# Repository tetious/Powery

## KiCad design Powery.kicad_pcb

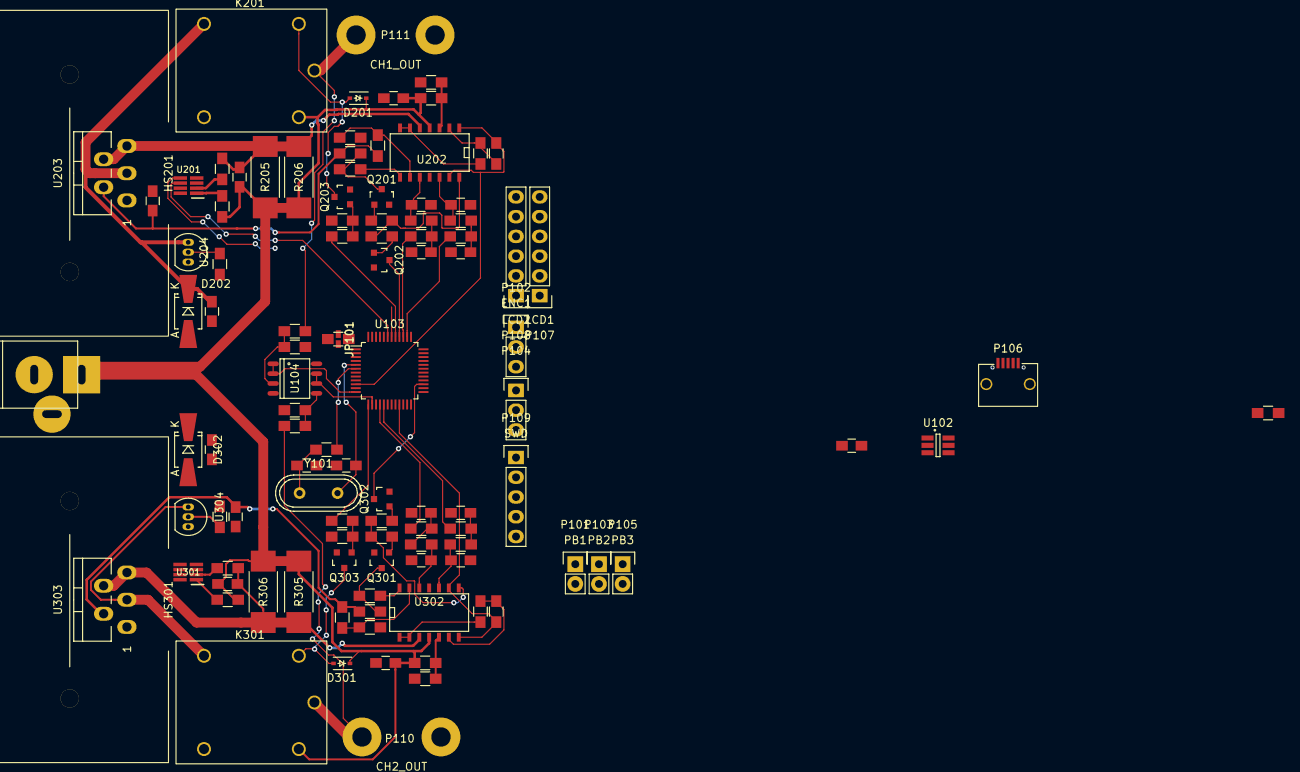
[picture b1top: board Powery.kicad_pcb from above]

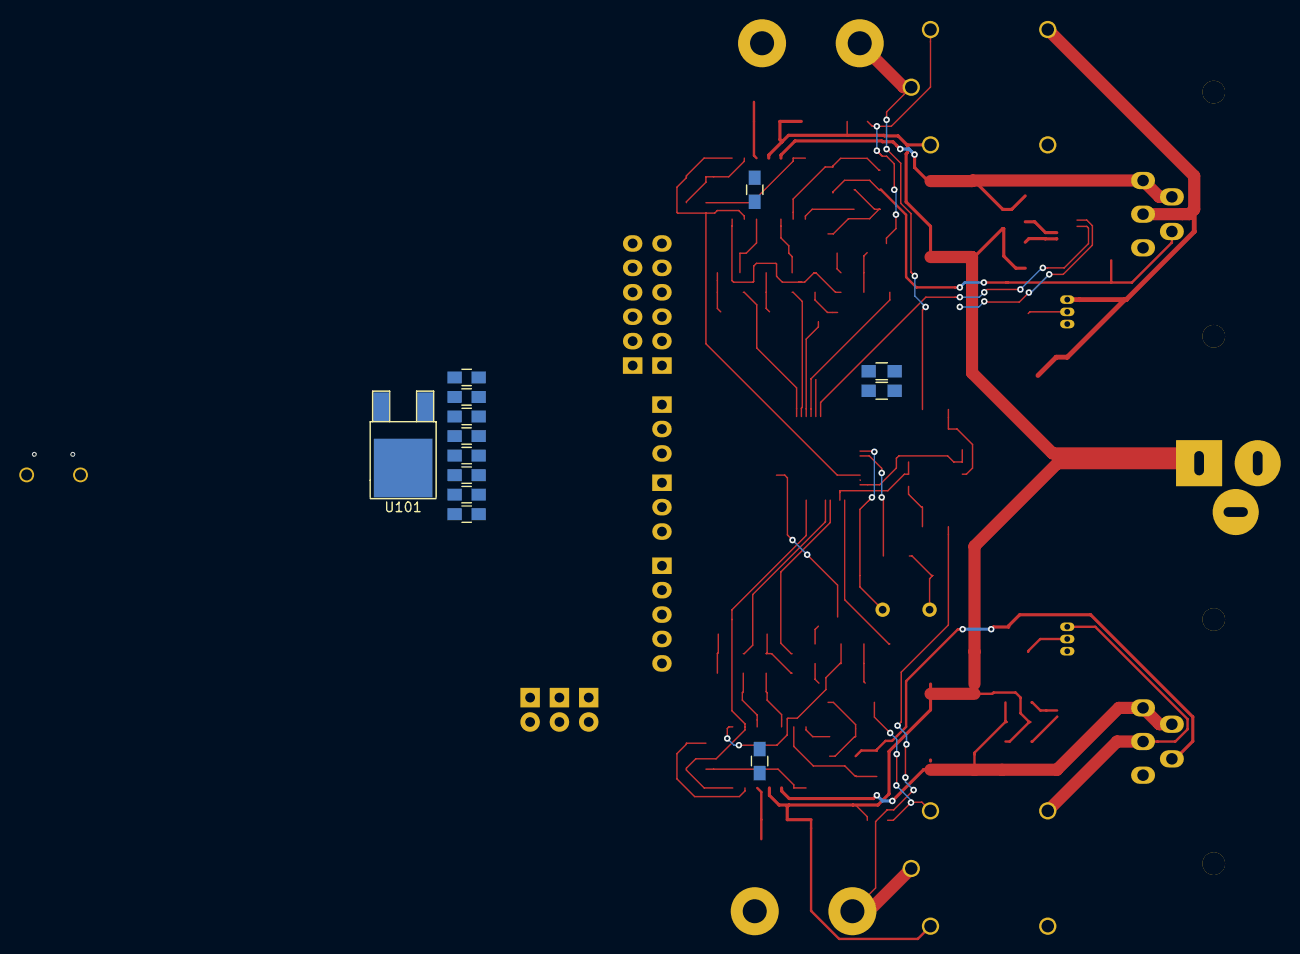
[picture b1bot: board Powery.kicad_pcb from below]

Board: 2 copper layers, 120 parts (13 on the bottom side), 87 nets.

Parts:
C101, C207, C208, C209, C307, C308, C309: 10uf; C_0805_HandSoldering
C102: 4.7uf; C_0805_HandSoldering
C103, C104, C105, C106, C107: 100nf; C_0805_HandSoldering
C108: 10nf; C_0805_HandSoldering
C109, C206, C306: 1uf; C_0805_HandSoldering
C110, C111: 20pf; C_0805_HandSoldering
C201, C301: NP; C_0805_HandSoldering
C202, C203, C204, C205, C302, C303, C304, C305: 0.1u; C_0805_HandSoldering
CON101: BARREL_JACK; JACK_ALIM
D201, D301: D; SOD-323
D202, D302: D; SMA-SMB_Universal_Handsoldering
HS201, HS301: HEATSINK; HS-TO220-20W
JP101: Jumper_NO_Small; MADW__SMD-solder-bridge-narrow
K201, K301: RELAY-SPDT; RELAY-SRD
P101: PB1; Pin_Header_Straight_1x02
P102: ENC1; Pin_Header_Straight_1x03
P103: PB2; Pin_Header_Straight_1x02
P104: ENC2; Pin_Header_Straight_1x03
P105: PB3; Pin_Header_Straight_1x02
P106: USB_OTG; USB_Micro-B-ebay
P107: LCD1; Pin_Header_Straight_1x06
P108: LCD2; Pin_Header_Straight_1x06
P109: SWD; Pin_Header_Straight_1x05
P110: CH2_OUT; WireConnection_2.50mmDrill
P111: CH1_OUT; WireConnection_2.50mmDrill
Q201, Q202, Q203, Q301, Q302, Q303: MMBT3904; SOT-23
R101, R102: 2.2k; R_0805_HandSoldering
R103: 4.7k; R_0805_HandSoldering
R104, R108, R109, R209, R212, R214, R215, R216, R220, R309, R312, R314, R315, R316, R320: 10k; R_0805_HandSoldering
R105: 220; R_0805_HandSoldering
R106, R107, R211, R311: 4.3k; R_0805_HandSoldering
R201, R202, R301, R302: 0; R_0805_HandSoldering
R203, R204, R207, R208, R210, R213, R303, R304, R307, R308, R310, R313: 100k; R_0805_HandSoldering
R205, R206, R305, R306: 0.22; R_2512_HandSoldering
R217, R219, R317, R319: 1k; R_0805_HandSoldering
R218, R221, R318, R321: 100; R_0805_HandSoldering
U101: LM1117; TO-252-2Lead
U102: AOZ8904; SOT-23-6_Handsoldering
U103: STM32F103C8Tx; LQFP-48_7x7mm_Pitch0.5mm
U104: LM258W; SO-8
U201, U301: INA219-SOT23; SOT-23-8
U202, U302: LM324; SOIC-14_N
U203, U303: LT3083; Pentawatt_Neutral_Staggered_Verical_TO220-5-T05D
U204, U304: LM334Z/NOPB; TO-92_Inline_Narrow_Oval
Y101: 8mhz; Crystal_HC49-U_Vertical

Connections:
+3V3: C102.1, C103.1, C104.1, C105.1, C106.1, C107.1, C108.1, C109.1, P107.1, P108.1, P109.1, R101.2, R102.1, R103.2, R104.1, U101.2, U103.1, U103.9, U103.24, U103.36, U103.48, U201.4, U301.4, U301.8
+12V: C101.1, C201.2, C206.1, C301.2, C306.1, CON101.1, D201.1, D301.1, K201.C1, K301.C1, R201.2, R205.2, R206.2, R209.2, R301.2, R305.2, R306.2, R309.2, U101.3, U104.8, U202.4, U302.4
/C1-I-LMT: Q202.3, U103.40
/C1-I-PWM: R204.2, U103.38
/C1-I-SENSE: R213.1, U103.10, U202.1, U202.13
/C1-V-PWM: R203.2, U103.39
/C1-V-SENSE: U103.12, U104.1, U104.2
/C2-I-LMT: Q302.3, U103.27
/C2-I-PWM: R304.2, U103.17
/C2-I-SENSE: R313.1, U103.21, U302.7, U302.9
/C2-V-PWM: R303.2, U103.16
/C2-V-SENSE: U103.14, U104.6, U104.7
/CH1_PWR: R219.2, U103.41
/CH2_PWR: R319.2, U103.13
/Channel1/12v-AS: C201.1, C207.2, R202.2, R205.1, R206.1, U202.5, U203.4, U203.5
/Channel1/OUT: K201.1, P111.1, R106.2
/Channel1/REG-OUT: C209.2, D202.1, K201.3, U203.3, U204.1
/Channel1/SET: C208.2, R214.1, R218.1, U203.2
/Channel2/12v-AS: C301.1, C307.2, R302.2, R305.1, R306.1, U302.3, U303.4, U303.5
/Channel2/OUT: K301.1, P110.1, R107.2
/Channel2/REG-OUT: C309.2, D302.1, K301.3, U303.3, U304.1
/Channel2/SET: C308.2, R314.1, R318.1, U303.2
/ENC_1A: P102.1, U103.45
/ENC_1B: P102.2, U103.46
/ENC_1PB: P102.3, U103.25
/ENC_2A: P104.1, U103.30
/ENC_2B: P104.2, U103.31
/ENC_2PB: P104.3, U103.29
/LCD1_CS: P107.3, U103.22
/LCD1_MD: P107.2, U103.15
/LCD2_CS: P108.3, U103.18
/LCD2_MD: P108.2, U103.19
/NRST: P109.5, U103.7
/PB_1: P101.1, U103.2
/PB_2: P103.1, U103.3
/PB_3: P105.1, U103.4
/SPI_MOSI: P107.5, P108.5, U103.28
/SPI_SCK: P107.4, P108.4, U103.26
/SWCLK: P109.2, U103.37
/SWDIO: P109.4, U103.34
/USB_DM: P106.2, U102.3, U103.32
/USB_DP: P106.3, R103.1, U102.1, U103.33
GND: C101.2, C102.2, C103.2, C104.2, C105.2, C106.2, C107.2, C108.2, C109.2, C110.1, C111.1, C202.2, C203.2, C204.2, C205.2, C206.2, C207.1, C208.1, C209.1, C302.2, C303.2, C304.2, C305.2, C306.2, C307.1, C308.1, C309.1, CON101.2, CON101.3, D202.2, D302.2, JP101.1, P101.2, P103.2, P105.2, P106.5, P106.6, P107.6, P108.6, P109.3, P110.2, P111.2, Q201.2, Q202.2, Q203.2, Q301.2, Q302.2, Q303.2, R108.1, R109.1, R210.2, R211.2, R220.2, R221.2, R310.2, R311.2, R320.2, R321.2, U101.1, U102.2, U103.8, U103.23, U103.35, U103.47, U104.4, U201.3, U201.7, U201.8, U202.11, U204.3, U301.3, U301.7, U302.11, U304.3
unnamed: C110.2, R105.1, Y101.1
unnamed: C111.2, U103.5, Y101.2
unnamed: C202.1, R203.1, R207.2
unnamed: C203.1, R204.1, R208.2
unnamed: C204.1, R207.1, U202.10
unnamed: C205.1, R208.1, U202.12
unnamed: C302.1, R303.1, R307.2
unnamed: C303.1, R304.1, R308.2
unnamed: C304.1, R307.1, U302.12
unnamed: C305.1, R308.1, U302.10
unnamed: D201.2, K201.C2, Q203.3
unnamed: D301.2, K301.C2, Q303.3
unnamed: JP101.2, R104.2, U103.44
unnamed: Q201.1, R215.1
unnamed: Q201.3, R217.1, R218.2
unnamed: Q202.1, R216.1
unnamed: Q203.1, R219.1, R220.1
unnamed: Q301.1, R315.1
unnamed: Q301.3, R317.1, R318.2
unnamed: Q302.1, R316.1
unnamed: Q303.1, R319.1, R320.1
unnamed: R105.2, U103.6
unnamed: R106.1, R108.2, U104.3
unnamed: R107.1, R109.2, U104.5
unnamed: R201.1, U201.1
unnamed: R202.1, U201.2
unnamed: R209.1, R210.1, U202.3
unnamed: R211.1, R214.2, U202.9
unnamed: R212.1, R213.2, U202.2
unnamed: R212.2, U202.6, U202.7
unnamed: R215.2, R216.2, U202.14
unnamed: R217.2, U202.8
unnamed: R221.1, U204.2
unnamed: R301.1, U301.1
unnamed: R302.1, U301.2
unnamed: R309.1, R310.1, U302.5
unnamed: R311.1, R314.2, U302.13
unnamed: R312.1, R313.2, U302.6
unnamed: R312.2, U302.1, U302.2
unnamed: R315.2, R316.2, U302.8
unnamed: R317.2, U302.14
unnamed: R321.1, U304.2
SCL: R101.1, U103.42, U201.5, U301.5
SDA: R102.2, U103.43, U201.6, U301.6

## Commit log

2016-08-17 Initial checkin. Schematic rev A complete.
2016-08-17 Oops.
2016-08-19 WIP layout.
2016-08-19 Partially routed one channel.
2016-08-23 More layout work.
